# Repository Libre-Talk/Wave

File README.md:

# Wave Mark 0 Hardware

*⛵️ Note that this repository is a work-in-progress. It will be updated and improved on over time.*

This repository contains all of the designs and technical details of the Wave Smart Speaker Prototype.

Each sub-directory represents a prototype device. Currently this consists of:
- [Wave Mark 0](./mk-0) - the first Mark 0 prototype

## Our open hardware principles
* **Copy our designs** – build your own
* **Modify our designs** – remixing is encouraged
* **Sell products based on our designs** – commercial use is permitted
* **Always keep the open license** – contribute your output back to the community
* **Credit the original author(s)** – like they do in science

## Feedback or ideas

We are always keen to hear from the community about ways to improve these designs. Whether you're a hacker, maker, engineer, or something else - join us in the:

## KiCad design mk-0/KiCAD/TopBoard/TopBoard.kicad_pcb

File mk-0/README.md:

# Wave Mk 0 - Prototype

## Kit Major Components
* ESP32-S3
* Mk 0 Motherboard
* Audio Chamber
* Single 10W Speaker with driver
* Elegant 3D printed enclosure
* Universal 12V power supply (USA, EU,UK, AUS, CCC)

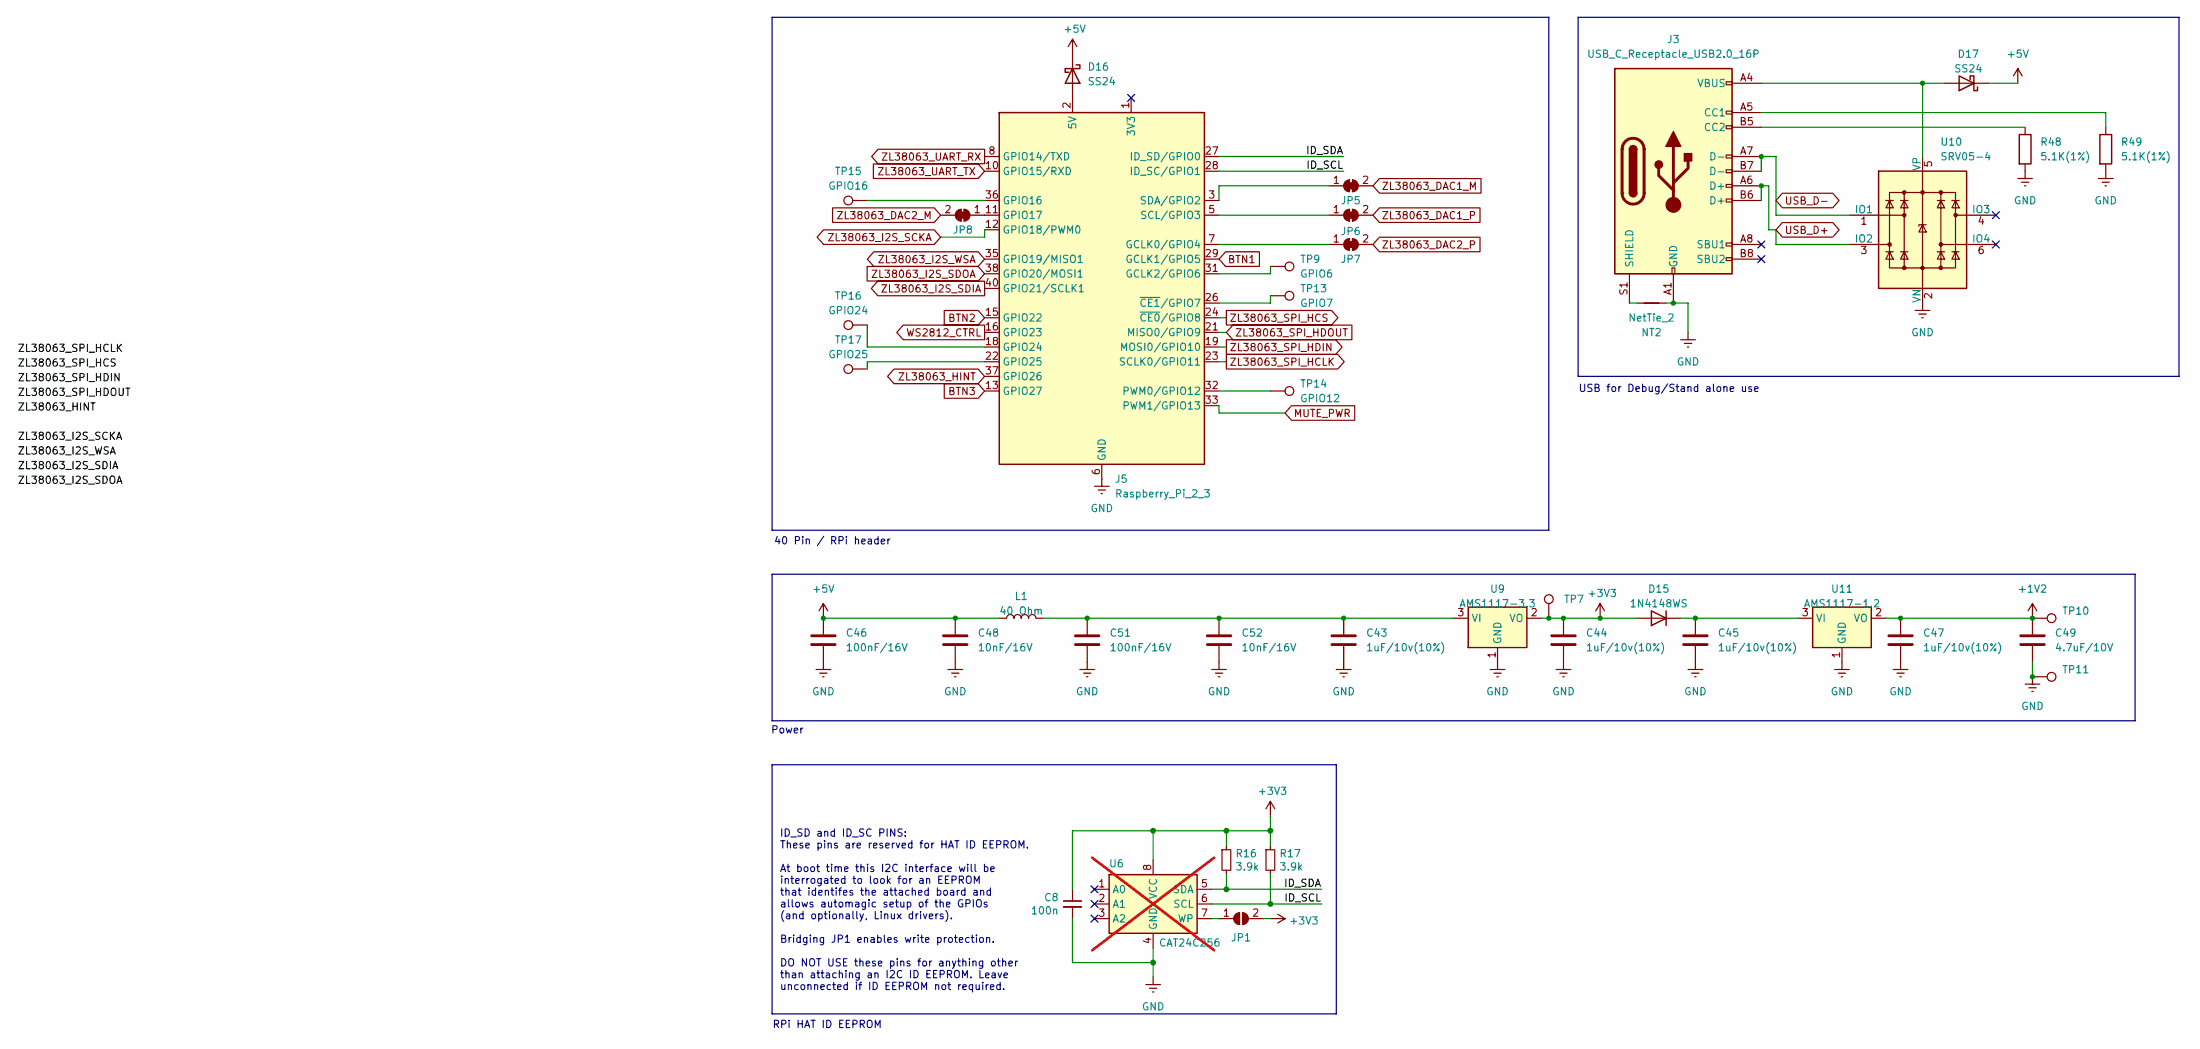
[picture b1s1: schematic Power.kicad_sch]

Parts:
C8: 100n; C_0402_1005Metric
C43, C44, C45, C47: 1uF/10v(10%); C_0402_1005Metric
C46, C51: 100nF/16V; C_0402_1005Metric
C48, C52: 10nF/16V; C_0402_1005Metric
C49: 4.7uF/10V; C_0402_1005Metric
D15: 1N4148WS; D_SOD-323F
D16, D17: SS24; D_SMA
J3: USB_C_Receptacle_USB2.0_16P; USB_C_Receptacle_G-Switch_GT-USB-7010ASV
J5: Raspberry_Pi_2_3; PinSocket_2x20_P2.54mm_Vertical_Through_SMD
JP1: ID_WP; SolderJumper-2_P1.3mm_Open_RoundedPad1.0x1.5mm
JP5, JP6, JP7, JP8: SolderJumper_2_Bridged; SolderJumper-2_P1.3mm_Bridged_RoundedPad1.0x1.5mm
L1: 40 Ohm; L_0603_1608Metric
NT2: NetTie_2; NetTie-2_SMD_Pad0.5mm
R16, R17: 3.9k; R_0402_1005Metric
R48, R49: 5.1K(1%); R_0402_1005Metric
TP7: 3V3; TestPoint_Pad_D1.0mm
TP9: GPIO6; TestPoint_Pad_D1.0mm
TP10: 1V2; TestPoint_Pad_D1.0mm
TP11: GND; TestPoint_Pad_D1.0mm
TP13: GPIO7; TestPoint_Pad_D1.0mm
TP14: GPIO12; TestPoint_Pad_D1.0mm
TP15: GPIO16; TestPoint_Pad_D1.0mm
TP16: GPIO24; TestPoint_Pad_D1.0mm
TP17: GPIO25; TestPoint_Pad_D1.0mm
U6: CAT24C256; SOIC-8_3.9x4.9mm_P1.27mm; not fitted
U9: AMS1117-3.3; SOT-223-3_TabPin2
U10: SRV05-4; SOT-23-6
U11: AMS1117-1.2; SOT-223-3_TabPin2

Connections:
+1V2: C47.1, C49.1, TP10.1, U11.2 (VO); also elsewhere on the board
+3V3: C8.1, C44.1, D15.2 (A), JP1.2 (B), R16.1, R17.1, TP7.1, U6.8 (VCC), U9.2 (VO); also elsewhere on the board
+5V: C46.1, C48.1, D16.1 (K), D17.1 (K), L1.1; also elsewhere on the board
/Power/ID_SCL: J5.28 (ID_SC/GPIO1), R17.2, U6.6 (SCL)
/Power/ID_SDA: J5.27 (ID_SD/GPIO0), R16.2, U6.5 (SDA)
BTN1: J5.29 (GCLK1/GPIO5); also elsewhere on the board
BTN2: J5.15 (GPIO22); also elsewhere on the board
BTN3: J5.13 (GPIO27); also elsewhere on the board
GND: C8.2, C43.2, C44.2, C45.2, C46.2, C47.2, C48.2, C49.2, C51.2, C52.2, J3.A1 (GND), J3.A12 (GND), J3.B1 (GND), J3.B12 (GND), J5.6 (GND), J5.9 (GND), J5.14 (GND), J5.20 (GND), J5.25 (GND), J5.30 (GND), J5.34 (GND), J5.39 (GND), NT2.1, R48.2, R49.2, TP11.1, U6.4 (GND), U9.1 (GND), U10.2 (VN), U11.1 (GND); also elsewhere on the board
MUTE_PWR: J5.33 (PWM1/GPIO13); also elsewhere on the board
unnamed: C45.1, D15.1 (K), U11.3 (VI)
unnamed: D16.2 (A), J5.2 (5V), J5.4 (5V)
unnamed: D17.2 (A), J3.A4 (VBUS), J3.A9 (VBUS), J3.B4 (VBUS), J3.B9 (VBUS), U10.5 (VP)
unnamed: J3.A5 (CC1), R49.1
unnamed: J3.B5 (CC2), R48.1
unnamed: J3.S1 (SHIELD), NT2.2
unnamed: J5.7 (GCLK0/GPIO4), JP7.1 (A)
unnamed: J5.31 (GCLK2/GPIO6), TP9.1
unnamed: J5.36 (GPIO16), TP15.1
unnamed: J5.11 (GPIO17), JP8.1 (A)
unnamed: J5.18 (GPIO24), TP16.1
unnamed: J5.22 (GPIO25), TP17.1
unnamed: J5.32 (PWM0/GPIO12), TP14.1
unnamed: J5.5 (SCL/GPIO3), JP6.1 (A)
unnamed: J5.3 (SDA/GPIO2), JP5.1 (A)
unnamed: J5.26 (~CE1/GPIO7), TP13.1
unnamed: JP1.1 (A), U6.7 (WP)
unnamed: C43.1, C51.1, C52.1, L1.2, U9.3 (VI)
USB_D+: J3.A6 (D+), J3.B6 (D+), U10.3 (IO2); also elsewhere on the board
USB_D-: J3.A7 (D-), J3.B7 (D-), U10.1 (IO1); also elsewhere on the board
WS2812_CTRL: J5.16 (GPIO23); also elsewhere on the board
ZL38063_DAC1_M: JP5.2 (B); also elsewhere on the board
ZL38063_DAC1_P: JP6.2 (B); also elsewhere on the board
ZL38063_DAC2_M: JP8.2 (B); also elsewhere on the board
ZL38063_DAC2_P: JP7.2 (B); also elsewhere on the board
ZL38063_HINT: J5.37 (GPIO26); also elsewhere on the board
ZL38063_I2S_SCKA: J5.12 (GPIO18/PWM0); also elsewhere on the board
ZL38063_I2S_SDIA: J5.40 (GPIO21/SCLK1); also elsewhere on the board
ZL38063_I2S_SDOA: J5.38 (GPIO20/MOSI1); also elsewhere on the board
ZL38063_I2S_WSA: J5.35 (GPIO19/MISO1); also elsewhere on the board
ZL38063_SPI_HCLK: J5.23 (SCLK0/GPIO11); also elsewhere on the board
ZL38063_SPI_HCS: J5.24 (~CE0/GPIO8); also elsewhere on the board
ZL38063_SPI_HDIN: J5.19 (MOSI0/GPIO10); also elsewhere on the board
ZL38063_SPI_HDOUT: J5.21 (MISO0/GPIO9); also elsewhere on the board
ZL38063_UART_RX: J5.8 (GPIO14/TXD); also elsewhere on the board
ZL38063_UART_TX: J5.10 (GPIO15/RXD); also elsewhere on the board

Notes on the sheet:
40 Pin / RPi header
USB for Debug/Stand alone use
Power
RPi HAT ID EEPROM
ID_SD and ID_SC PINS: These pins are reserved for HAT ID EEPROM. At boot time this I2C interface will be interrogated to look for an EEPROM that identifes the attached board and allows automagic setup of the GPIOs (and optionally, Linux drivers). Bridging JP1 enables write protection. DO NOT USE th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

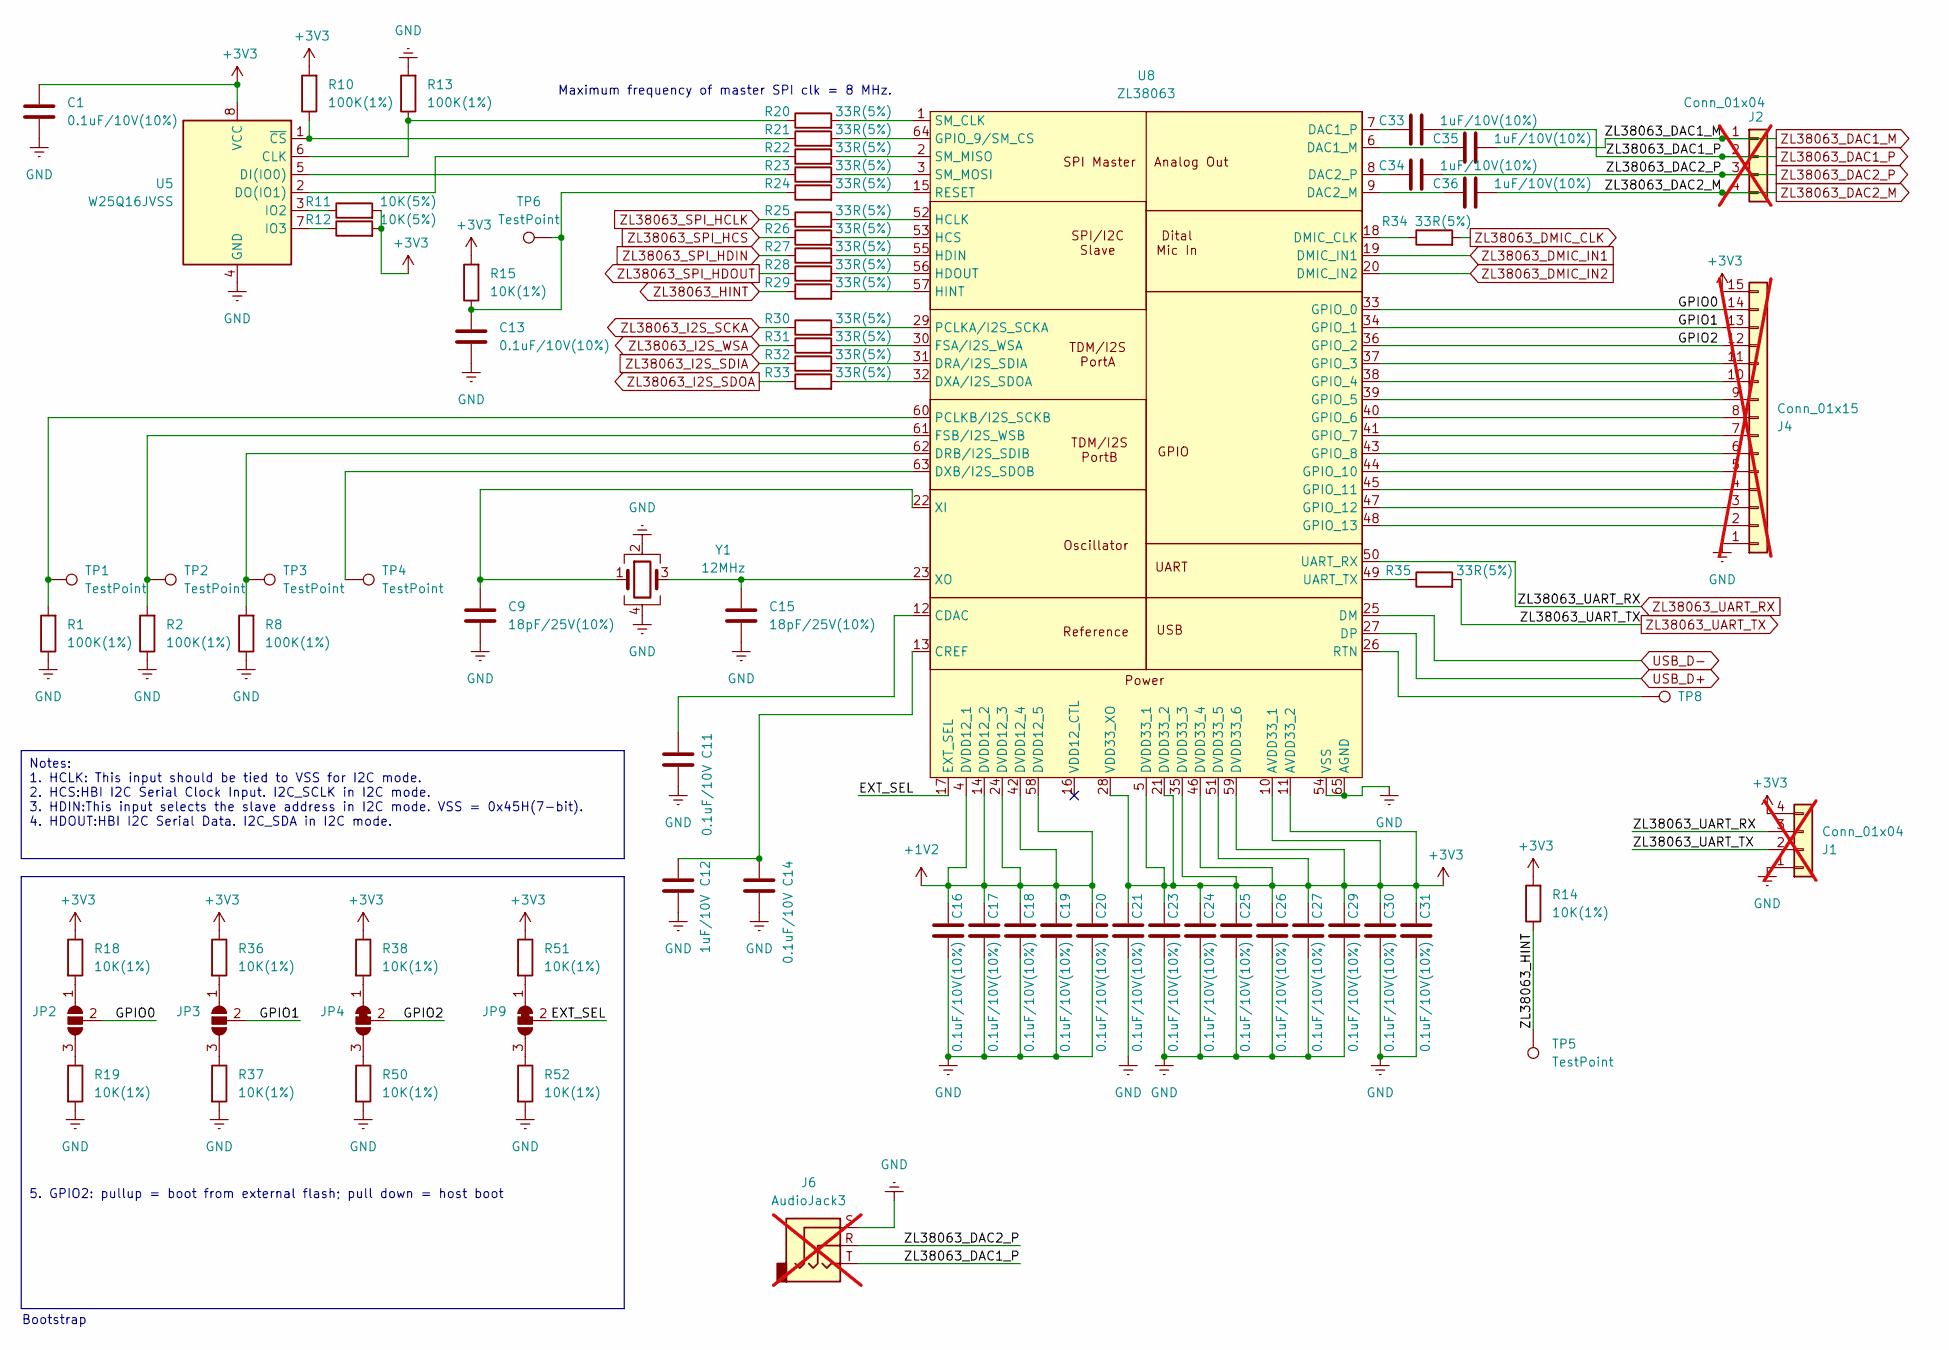
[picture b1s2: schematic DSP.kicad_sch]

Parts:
C1, C13, C16, C17, C18, C19, C20, C21, C23, C24, C25, C26, C27, C29, C30, C31: 0.1uF/10V(10%); C_0402_1005Metric
C9, C15: 18pF/25V(10%); C_0402_1005Metric
C11, C14: 0.1uF/10V; C_0402_1005Metric
C12: 1uF/10V; C_0402_1005Metric
C33, C34, C35, C36: 1uF/10V(10%); C_0402_1005Metric
J1, J2: Conn_01x04; PinHeader_1x04_P2.54mm_Vertical; not fitted
J4: Conn_01x15; PinHeader_1x15_P2.54mm_Vertical; not fitted
J6: AudioJack3; Jack_3.5mm_CUI_SJ1-3533NG_Horizontal; not fitted
JP2, JP3: SolderJumper_3_Open; SolderJumper-3_P1.3mm_Open_RoundedPad1.0x1.5mm
JP4, JP9: SolderJumper_3_Bridged12; SolderJumper-3_P1.3mm_Bridged12_RoundedPad1.0x1.5mm
R1, R2, R8, R10, R13: 100K(1%); R_0402_1005Metric
R11, R12: 10K(5%); R_0402_1005Metric
R14, R15, R18, R19, R36, R37, R38, R50, R51, R52: 10K(1%); R_0402_1005Metric
R20, R21, R22, R23, R24, R25, R26, R27, R28, R29, R30, R31, R32, R33, R34, R35: 33R(5%); R_0402_1005Metric
TP1, TP2, TP3, TP4, TP5, TP6, TP8: TestPoint; TestPoint_Pad_D1.0mm
U5: W25Q16JVSS; SOIC-8_3.9x4.9mm_P1.27mm
U8: ZL38063; QFN-64-1EP_9x9mm_P0.5mm_EP7.3x7.3mm_ThermalVias
Y1: 12MHz; Crystal_SMD_3225-4Pin_3.2x2.5mm

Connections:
+1V2: C16.1, C17.1, C18.1, C19.1, C20.1, U8.4 (DVDD12_1), U8.14 (DVDD12_2), U8.24 (DVDD12_3), U8.42 (DVDD12_4), U8.58 (DVDD12_5); also elsewhere on the board
+3V3: C1.1, C21.1, C23.1, C24.1, C25.1, C26.1, C27.1, C29.1, C30.1, C31.1, J1.4, J4.15, R10.2, R11.2, R12.2, R14.2, R15.2, R18.1, R36.1, R38.1, R51.1, U5.8 (VCC), U8.5 (DVDD33_1), U8.10 (AVDD33_1), U8.11 (AVDD33_2), U8.21 (DVDD33_2), U8.28 (VDD33_XO), U8.35 (DVDD33_3), U8.46 (DVDD33_4), U8.51 (DVDD33_5), U8.59 (DVDD33_6); also elsewhere on the board
/DSP/EXT_SEL: JP9.2 (C), U8.17 (EXT_SEL)
/DSP/GPIO0: J4.14, JP2.2 (C), U8.33 (GPIO_0)
/DSP/GPIO1: J4.13, JP3.2 (C), U8.34 (GPIO_1)
/DSP/GPIO2: J4.12, JP4.2 (C), U8.36 (GPIO_2)
GND: C1.2, C9.2, C11.2, C12.2, C13.2, C14.2, C15.2, C16.2, C17.2, C18.2, C19.2, C20.2, C21.2, C23.2, C24.2, C25.2, C26.2, C27.2, C29.2, C30.2, C31.2, J1.1, J4.1, J6.S, R1.1, R2.1, R8.1, R13.2, R19.2, R37.2, R50.2, R52.2, U5.4 (GND), U8.54 (VSS), U8.65 (AGND), Y1.2, Y1.4; also elsewhere on the board
unnamed: C13.1, R15.1, R24.1, TP6.1
unnamed: J4.2, U8.48 (GPIO_13)
unnamed: J4.3, U8.47 (GPIO_12)
unnamed: J4.4, U8.45 (GPIO_11)
unnamed: J4.5, U8.44 (GPIO_10)
unnamed: J4.6, U8.43 (GPIO_8)
unnamed: J4.7, U8.41 (GPIO_7)
unnamed: J4.8, U8.40 (GPIO_6)
unnamed: J4.9, U8.39 (GPIO_5)
unnamed: J4.10, U8.38 (GPIO_4)
unnamed: J4.11, U8.37 (GPIO_3)
unnamed: JP2.1 (A), R18.2
unnamed: JP2.3 (B), R19.1
unnamed: JP3.1 (A), R36.2
unnamed: JP3.3 (B), R37.1
unnamed: JP4.1 (A), R38.2
unnamed: JP4.3 (B), R50.1
unnamed: JP9.1 (A), R51.2
unnamed: JP9.3 (B), R52.1
unnamed: R13.1, R20.1, U5.6 (CLK)
unnamed: R23.1, U5.5 (DI(IO0))
unnamed: R22.1, U5.2 (DO(IO1))
unnamed: R11.1, U5.3 (IO2)
unnamed: R12.1, U5.7 (IO3)
unnamed: R10.1, R21.1, U5.1 (~CS)
unnamed: C11.1, U8.12 (CDAC)
unnamed: C12.1, C14.1, U8.13 (CREF)
unnamed: C35.1, U8.6 (DAC1_M)
unnamed: C33.1, U8.7 (DAC1_P)
unnamed: C36.1, U8.9 (DAC2_M)
unnamed: C34.1, U8.8 (DAC2_P)
unnamed: R34.1, U8.18 (DMIC_CLK)
unnamed: R32.2, U8.31 (DRA/I2S_SDIA)
unnamed: R8.2, TP3.1, U8.62 (DRB/I2S_SDIB)
unnamed: R33.2, U8.32 (DXA/I2S_SDOA)
unnamed: TP4.1, U8.63 (DXB/I2S_SDOB)
unnamed: R31.2, U8.30 (FSA/I2S_WSA)
unnamed: R2.2, TP2.1, U8.61 (FSB/I2S_WSB)
unnamed: R21.2, U8.64 (GPIO_9/SM_CS)
unnamed: R25.2, U8.52 (HCLK)
unnamed: R26.2, U8.53 (HCS)
unnamed: R27.2, U8.55 (HDIN)
unnamed: R28.2, U8.56 (HDOUT)
unnamed: R29.2, U8.57 (HINT)
unnamed: R30.2, U8.29 (PCLKA/I2S_SCKA)
unnamed: R1.2, TP1.1, U8.60 (PCLKB/I2S_SCKB)
unnamed: R24.2, U8.15 (RESET)
unnamed: TP8.1, U8.26 (RTN)
unnamed: R20.2, U8.1 (SM_CLK)
unnamed: R22.2, U8.2 (SM_MISO)
unnamed: R23.2, U8.3 (SM_MOSI)
unnamed: R35.1, U8.49 (UART_TX)
unnamed: C9.1, U8.22 (XI), Y1.1
unnamed: C15.1, U8.23 (XO), Y1.3
USB_D+: U8.27 (DP); also elsewhere on the board
USB_D-: U8.25 (DM); also elsewhere on the board
ZL38063_DAC1_M: C35.2, J2.1; also elsewhere on the board
ZL38063_DAC1_P: C33.2, J2.2, J6.T; also elsewhere on the board
ZL38063_DAC2_M: C36.2, J2.4; also elsewhere on the board
ZL38063_DAC2_P: C34.2, J2.3, J6.R; also elsewhere on the board
ZL38063_DMIC_CLK: R34.2; also elsewhere on the board
ZL38063_DMIC_IN1: U8.19 (DMIC_IN1); also elsewhere on the board
ZL38063_DMIC_IN2: U8.20 (DMIC_IN2); also elsewhere on the board
ZL38063_HINT: R14.1, R29.1, TP5.1; also elsewhere on the board
ZL38063_I2S_SCKA: R30.1; also elsewhere on the board
ZL38063_I2S_SDIA: R32.1; also elsewhere on the board
ZL38063_I2S_SDOA: R33.1; also elsewhere on the board
ZL38063_I2S_WSA: R31.1; also elsewhere on the board
ZL38063_SPI_HCLK: R25.1; also elsewhere on the board
ZL38063_SPI_HCS: R26.1; also elsewhere on the board
ZL38063_SPI_HDIN: R27.1; also elsewhere on the board
ZL38063_SPI_HDOUT: R28.1; also elsewhere on the board
ZL38063_UART_RX: J1.3, U8.50 (UART_RX); also elsewhere on the board
ZL38063_UART_TX: J1.2, R35.2; also elsewhere on the board

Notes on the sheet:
5. GPIO2: pullup = boot from external flash; pull down = host boot
Notes: 1. HCLK: This input should be tied to VSS for I2C mode. 2. HCS:HBI I2C Serial Clock Input. I2C_SCLK in I2C mode. 3. HDIN:This input selects the slave address in I2C mode. VSS = 0x45H(7-bit). 4. HDOUT:HBI I2C Serial Data. I2C_SDA in I2C mode.
Maximum frequency of master SPI clk = 8 MHz.
Bootstrap

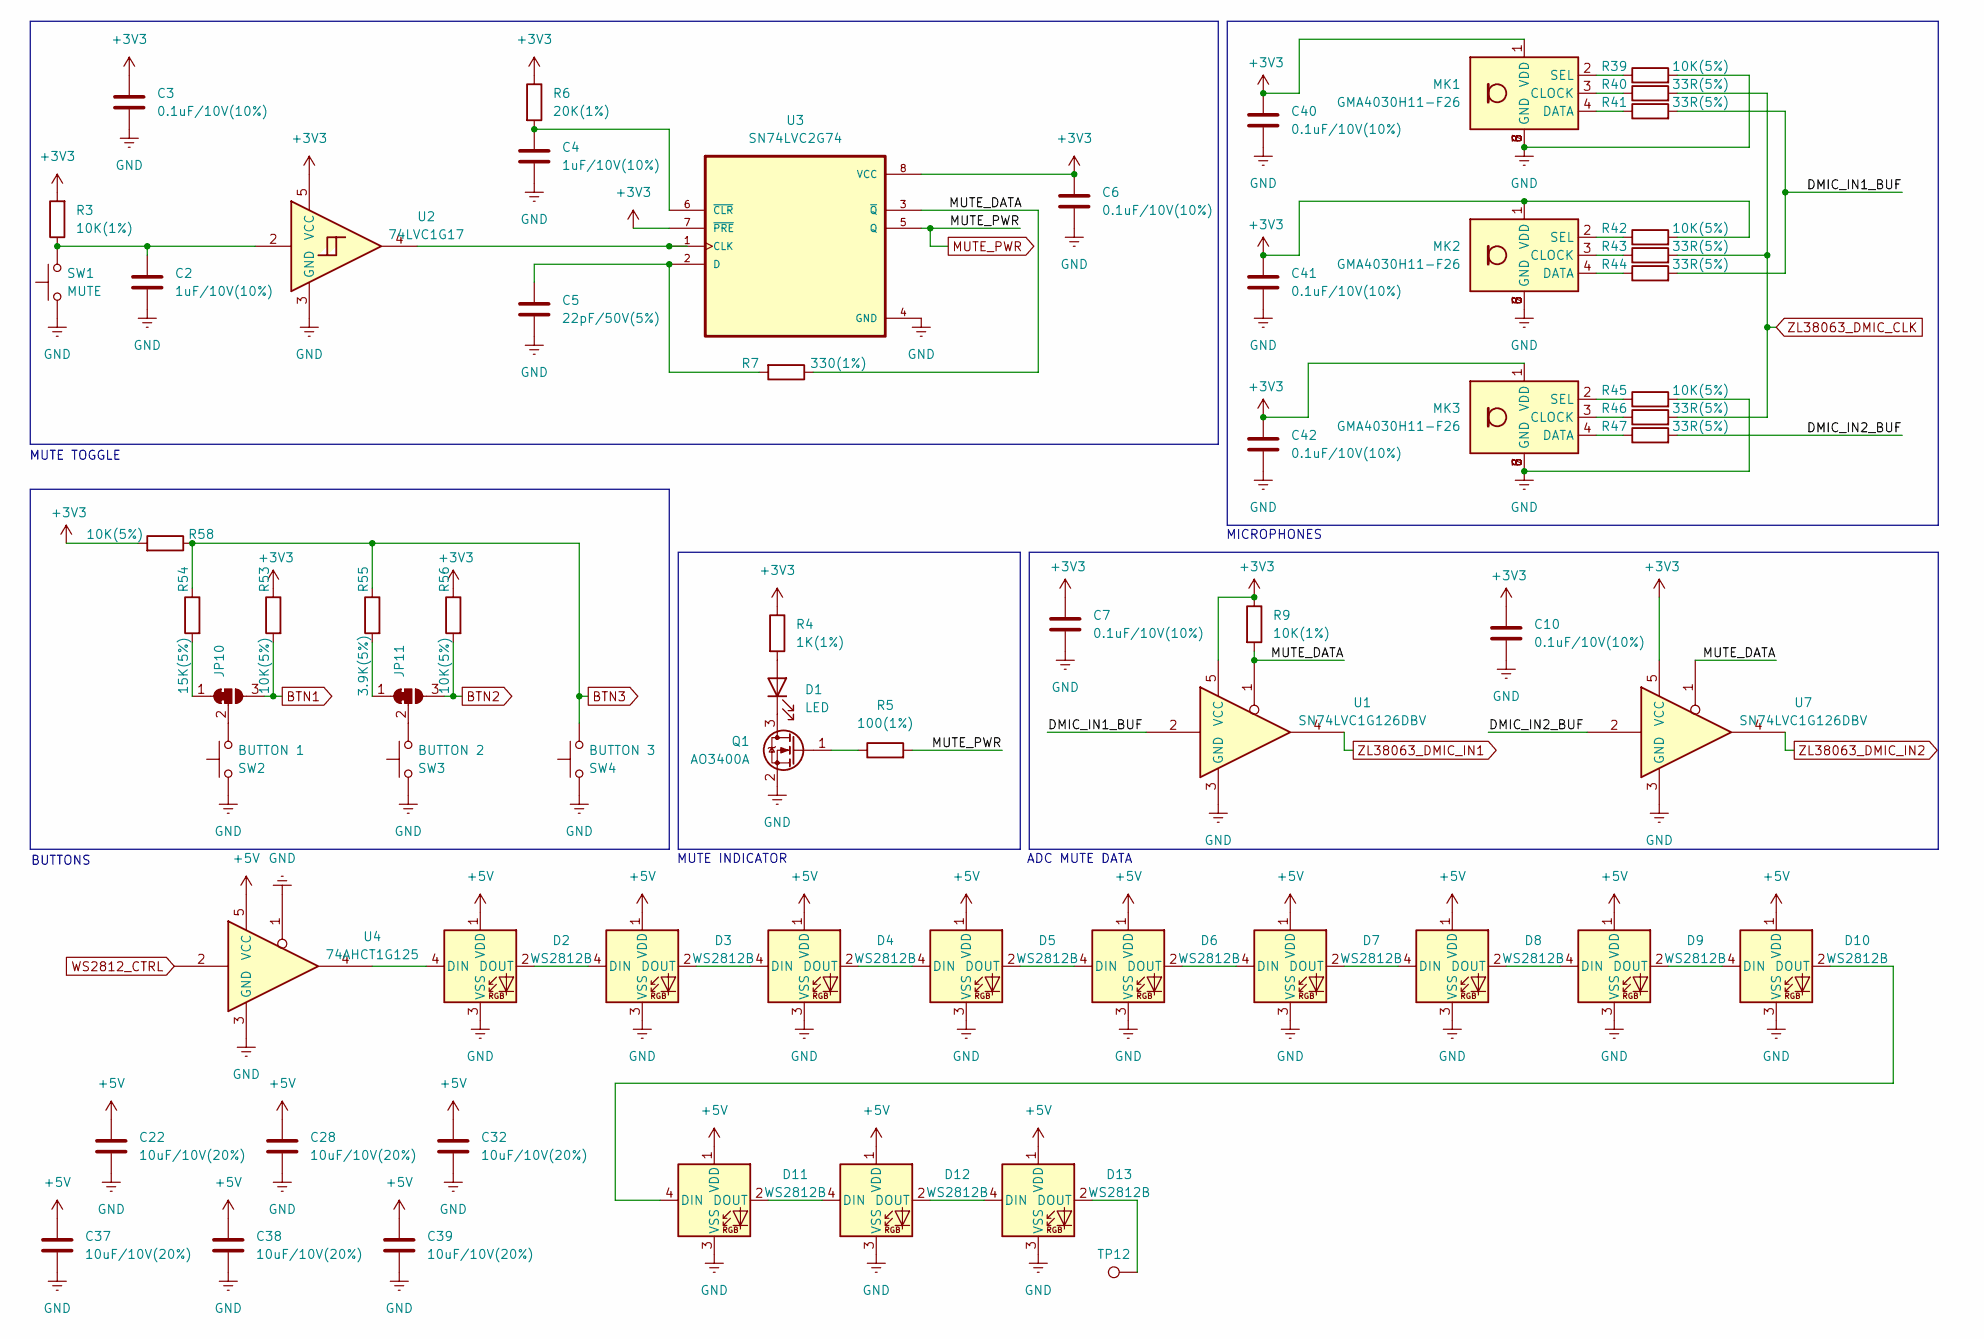
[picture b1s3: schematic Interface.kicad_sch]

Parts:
C2, C4: 1uF/10V(10%); C_0402_1005Metric
C3, C6, C7, C10, C40, C41, C42: 0.1uF/10V(10%); C_0402_1005Metric
C5: 22pF/50V(5%); C_0402_1005Metric
C22, C28, C32, C37, C38, C39: 10uF/10V(20%); C_0402_1005Metric
D1: LED; LED_0603_1608Metric
D2, D3, D4, D5, D6, D7, D8, D9, D10, D11, D12, D13: WS2812B; LED_WS2812B_PLCC4_5.0x5.0mm_P3.2mm
JP10, JP11: SolderJumper_3_Bridged12; SolderJumper-3_P1.3mm_Bridged12_RoundedPad1.0x1.5mm
MK1, MK2, MK3: GMA4030H11-F26; XDCR_CMM-4030DT-26154-TR
Q1: AO3400A; SOT-23
R3, R9: 10K(1%); R_0402_1005Metric
R4: 1K(1%); R_0402_1005Metric
R5: 100(1%); R_0402_1005Metric
R6: 20K(1%); R_0402_1005Metric
R7: 330(1%); R_0402_1005Metric
R39, R42, R45, R53, R56, R58: 10K(5%); R_0402_1005Metric
R40, R41, R43, R44, R46, R47: 33R(5%); R_0402_1005Metric
R54: 15K(5%); R_0402_1005Metric
R55: 3.9K(5%); R_0402_1005Metric
SW1: MUTE; SW_SPST_PTS645
SW2: BUTTON 1; SW_SPST_PTS645
SW3: BUTTON 2; SW_SPST_PTS645
SW4: BUTTON 3; SW_SPST_PTS645
TP12: TestPoint; TestPoint_Pad_D1.0mm
U1, U7: SN74LVC1G126DBV; SOT-23-5
U2: 74LVC1G17; SOT-23-5
U3: SN74LVC2G74; VSSOP-8_2.4x2.1mm_P0.5mm
U4: 74AHCT1G125; SOT-23-5

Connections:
+3V3: C3.1, C6.1, C7.1, C10.1, C40.1, C41.1, C42.1, MK1.1 (VDD), MK2.1 (VDD), MK3.1 (VDD), R3.2, R4.1, R6.1, R9.1, R42.2, R53.1, R56.1, R58.2, U1.5 (VCC), U2.5 (VCC), U3.7 (~PRE), U3.8 (VCC), U7.5 (VCC); also elsewhere on the board
+5V: C22.1, C28.1, C32.1, C37.1, C38.1, C39.1, D2.1 (VDD), D3.1 (VDD), D4.1 (VDD), D5.1 (VDD), D6.1 (VDD), D7.1 (VDD), D8.1 (VDD), D9.1 (VDD), D10.1 (VDD), D11.1 (VDD), D12.1 (VDD), D13.1 (VDD), U4.5 (VCC); also elsewhere on the board
/Interface/DMIC_IN1_BUF: R41.2, R44.2, U1.2
/Interface/DMIC_IN2_BUF: R47.2, U7.2
/Interface/MUTE_DATA: R7.1, R9.2, U1.1, U3.3 (~Q), U7.1
BTN1: JP10.3 (B), R53.2; also elsewhere on the board
BTN2: JP11.3 (B), R56.2; also elsewhere on the board
BTN3: R54.1, R55.1, R58.1, SW4.1; also elsewhere on the board
GND: C2.2, C3.2, C4.2, C5.2, C6.2, C7.2, C10.2, C22.2, C28.2, C32.2, C37.2, C38.2, C39.2, C40.2, C41.2, C42.2, D2.3 (VSS), D3.3 (VSS), D4.3 (VSS), D5.3 (VSS), D6.3 (VSS), D7.3 (VSS), D8.3 (VSS), D9.3 (VSS), D10.3 (VSS), D11.3 (VSS), D12.3 (VSS), D13.3 (VSS), MK1.5 (GND), MK1.6 (GND), MK1.7 (GND), MK1.8 (GND), MK2.5 (GND), MK2.6 (GND), MK2.7 (GND), MK2.8 (GND), MK3.5 (GND), MK3.6 (GND), MK3.7 (GND), MK3.8 (GND), Q1.2 (S), R39.2, R45.2, SW1.1, SW2.2, SW3.2, SW4.2, U1.3 (GND), U2.3 (GND), U3.4 (GND), U4.1, U4.3 (GND), U7.3 (GND); also elsewhere on the board
MUTE_PWR: R5.2, U3.5 (Q); also elsewhere on the board
unnamed: C2.1, R3.1, SW1.2, U2.2
unnamed: D1.2 (A), R4.2
unnamed: D1.1 (K), Q1.3 (D)
unnamed: D2.4 (DIN), U4.4
unnamed: D2.2 (DOUT), D3.4 (DIN)
unnamed: D3.2 (DOUT), D4.4 (DIN)
unnamed: D4.2 (DOUT), D5.4 (DIN)
unnamed: D5.2 (DOUT), D6.4 (DIN)
unnamed: D6.2 (DOUT), D7.4 (DIN)
unnamed: D7.2 (DOUT), D8.4 (DIN)
unnamed: D8.2 (DOUT), D9.4 (DIN)
unnamed: D9.2 (DOUT), D10.4 (DIN)
unnamed: D10.2 (DOUT), D11.4 (DIN)
unnamed: D11.2 (DOUT), D12.4 (DIN)
unnamed: D12.2 (DOUT), D13.4 (DIN)
unnamed: D13.2 (DOUT), TP12.1
unnamed: JP10.1 (A), R54.2
unnamed: JP10.2 (C), SW2.1
unnamed: JP11.1 (A), R55.2
unnamed: JP11.2 (C), SW3.1
unnamed: MK1.3 (CLOCK), R40.1
unnamed: MK1.4 (DATA), R41.1
unnamed: MK1.2 (SEL), R39.1
unnamed: MK2.3 (CLOCK), R43.1
unnamed: MK2.4 (DATA), R44.1
unnamed: MK2.2 (SEL), R42.1
unnamed: MK3.3 (CLOCK), R46.1
unnamed: MK3.4 (DATA), R47.1
unnamed: MK3.2 (SEL), R45.1
unnamed: Q1.1 (G), R5.1
unnamed: U2.4, U3.1 (CLK)
unnamed: C5.1, R7.2, U3.2 (D)
unnamed: C4.1, R6.2, U3.6 (~CLR)
WS2812_CTRL: U4.2; also elsewhere on the board
ZL38063_DMIC_CLK: R40.2, R43.2, R46.2; also elsewhere on the board
ZL38063_DMIC_IN1: U1.4; also elsewhere on the board
ZL38063_DMIC_IN2: U7.4; also elsewhere on the board

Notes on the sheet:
MUTE INDICATOR
BUTTONS
ADC MUTE DATA
MICROPHONES
MUTE TOGGLE

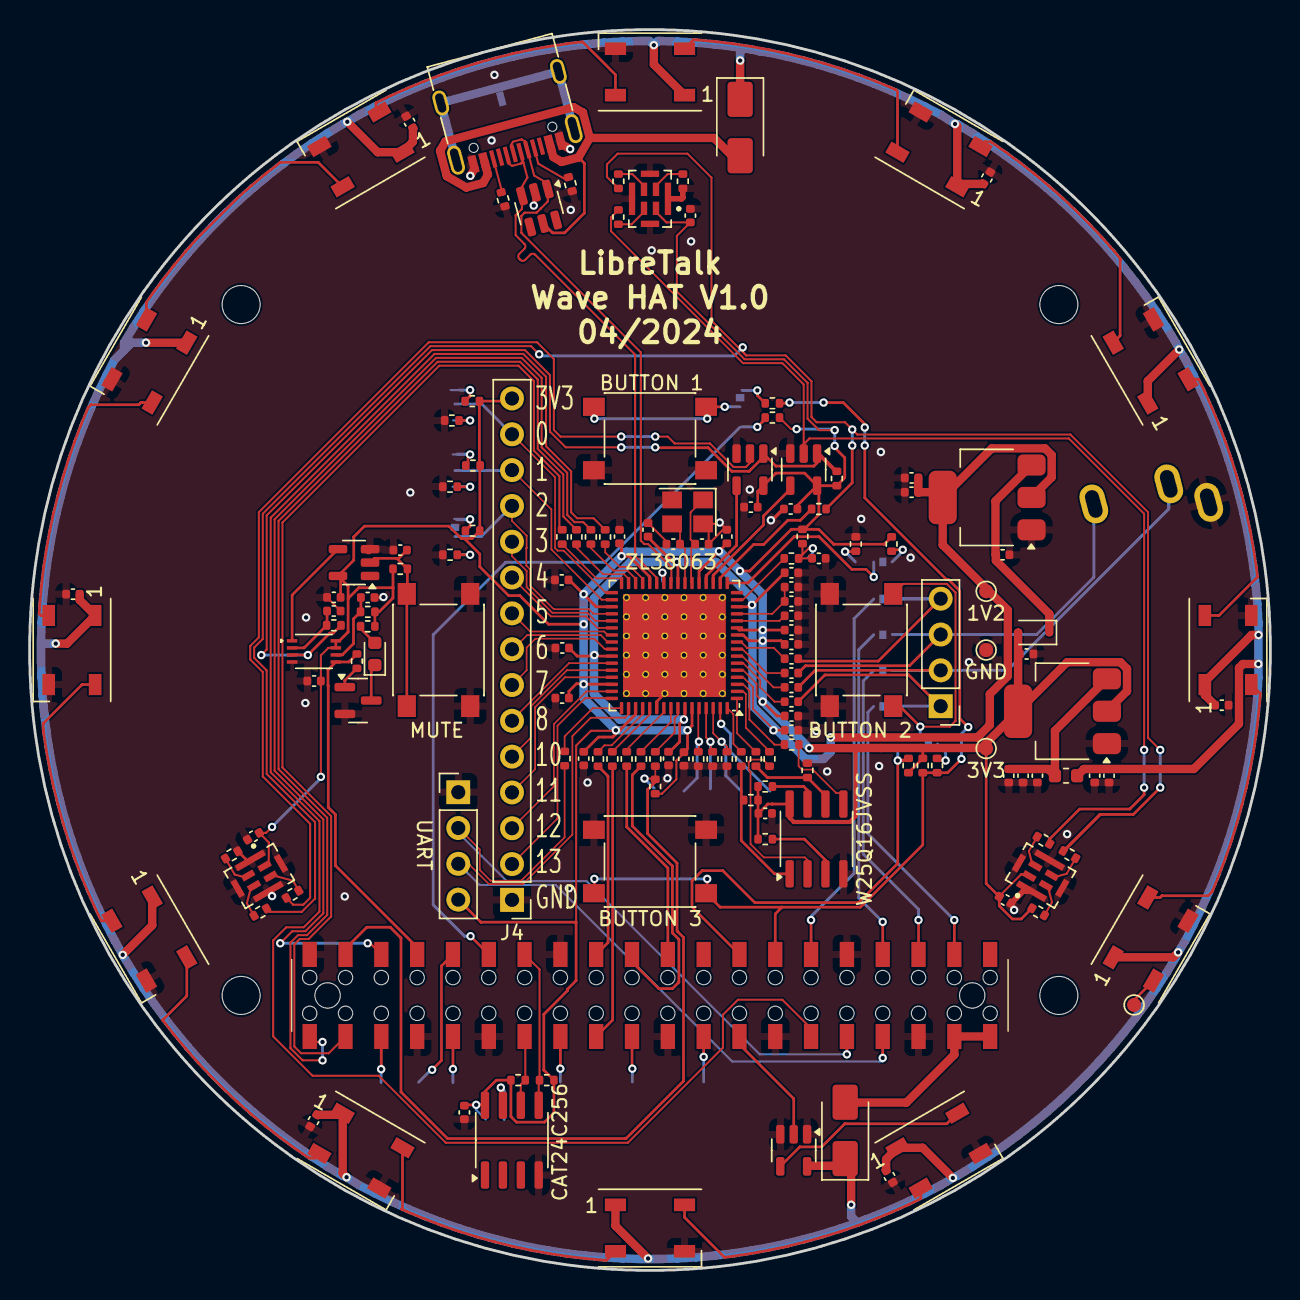
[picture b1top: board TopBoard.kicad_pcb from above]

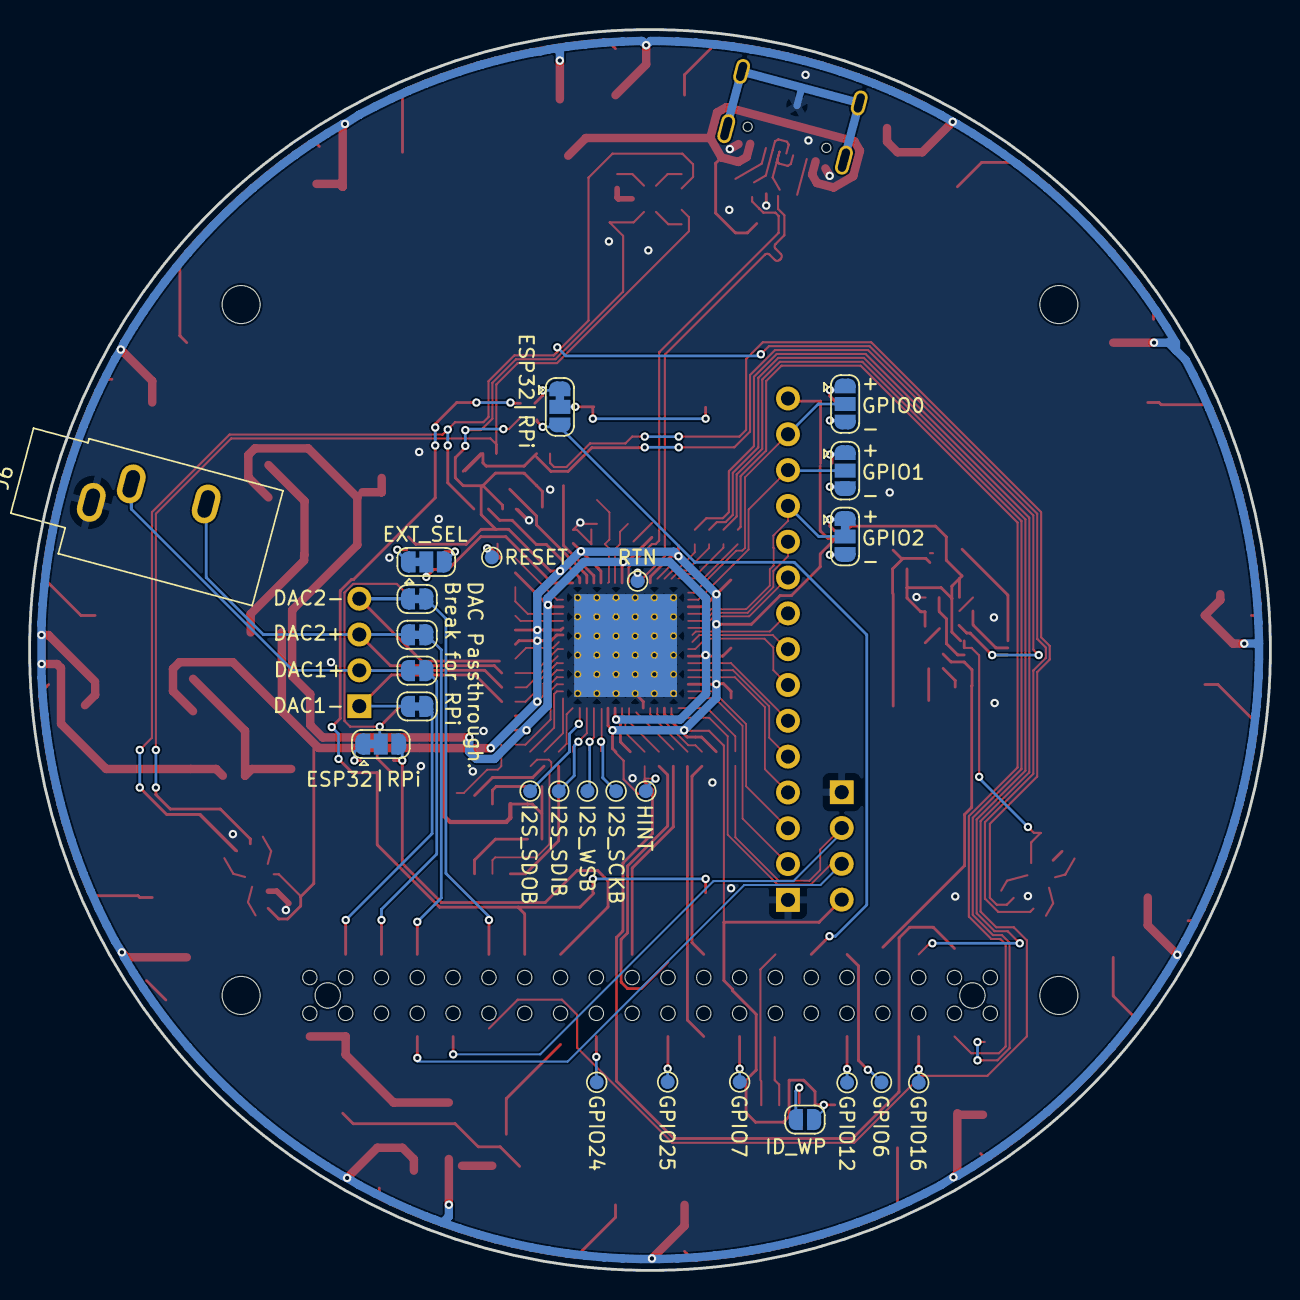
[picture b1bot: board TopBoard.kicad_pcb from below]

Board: 2 copper layers, 88.0 x 88.0 mm, 184 parts (26 on the bottom side), 143 nets.

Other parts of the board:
MH1, MH2, MH3, MH4: MountingHole_2.7mm_M2.5

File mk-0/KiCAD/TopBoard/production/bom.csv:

Designator,Footprint,Quantity,Value,LCSC Part #
"C1, C10, C13, C16, C17, C18, C19, C20, C21, C23, C24, C25, C26, C27, C29, C3, C30, C31, C40, C41, C42, C6, C7",0402,23,0.1uF/10V(10%),
"C11, C14",0402,2,0.1uF/10V,
C12,0402,1,1uF/10V,
"C15, C9",0402,2,18pF/25V(10%),
"C2, C33, C34, C35, C36, C4, C43, C44, C45, C47",0402,10,1uF/10V(10%),
"C22, C28, C32, C37, C38, C39",0402,6,10uF/10V(20%),
"C46, C51",0402,2,100nF/16V,
"C48, C52",0402,2,10nF/16V,
C49,0402,1,4.7uF/10V,
C5,0402,1,22pF/50V(5%),
C8,0402,1,100n,
D1,0603,1,LED,
"D10, D11, D12, D13, D2, D3, D4, D5, D6, D7, D8, D9",LED_WS2812B_PLCC4_5.0x5.0mm_P3.2mm,12,WS2812B,
D15,D_SOD-323F,1,1N4148WS,
"D16, D17",D_SMA,2,SS24,
J3,USB_C_Receptacle_G-Switch_GT-USB-7010ASV,1,USB_C_Receptacle_USB2.0_16P,
J5,PinSocket_2x20_P2.54mm_Vertical_Through_SMD,1,Raspberry_Pi_2_3,
JP1,SolderJumper-2_P1.3mm_Open_RoundedPad1.0x1.5mm,1,ID_WP,
"JP10, JP11, JP4, JP9",SolderJumper-3_P1.3mm_Bridged12_RoundedPad1.0x1.5mm,4,SolderJumper_3_Bridged12,
"JP2, JP3",SolderJumper-3_P1.3mm_Open_RoundedPad1.0x1.5mm,2,SolderJumper_3_Open,
"JP5, JP6, JP7, JP8",SolderJumper-2_P1.3mm_Bridged_RoundedPad1.0x1.5mm,4,SolderJumper_2_Bridged,
L1,0603,1,40 Ohm,
"MK1, MK2, MK3",XDCR_CMM-4030DT-26154-TR,3,GMA4030H11-F26,
Q1,SOT-23,1,AO3400A,
"R1, R10, R13, R2, R8",0402,5,100K(1%),
"R11, R12, R39, R42, R45, R53, R56, R58",0402,8,10K(5%),
"R14, R15, R18, R19, R3, R36, R37, R38, R50, R51, R52, R9",0402,12,10K(1%),
"R16, R17",0402,2,3.9k,
"R20, R21, R22, R23, R24, R25, R26, R27, R28, R29, R30, R31, R32, R33, R34, R35, R40, R41, R43, R44, R46, R47",0402,22,33R(5%),
R4,0402,1,1K(1%),
"R48, R49",0402,2,5.1K(1%),
R5,0402,1,100(1%),
R54,0402,1,15K(5%),
R55,0402,1,3.9K(5%),
R6,0402,1,20K(1%),
R7,0402,1,330(1%),
"SW1, SW2, SW3, SW4",SW_SPST_PTS645,4,SW_Push,
"TP1, TP10, TP11, TP12, TP2, TP3, TP4, TP5, TP6, TP7, TP8",TestPoint_Pad_D1.0mm,11,TestPoint,
"U1, U7",SOT-23-5,2,SN74LVC1G126DBV,
U10,SOT-23-6,1,SRV05-4,
U11,SOT-223-3_TabPin2,1,AMS1117-1.2,
U2,SOT-23-5,1,74LVC1G17,
U3,VSSOP-8_2.4x2.1mm_P0.5mm,1,SN74LVC2G74,
U4,SOT-23-5,1,74AHCT1G125,
U5,SOIC-8_3.9x4.9mm_P1.27mm,1,W25Q16JVSS,
U8,QFN-64-1EP_9x9mm_P0.5mm_EP7.3x7.3mm_ThermalVias,1,ZL38063,
U9,SOT-223-3_TabPin2,1,AMS1117-3.3,
Y1,Crystal_SMD_3225-4Pin_3.2x2.5mm,1,12MHz,
